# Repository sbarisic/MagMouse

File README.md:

# MagMouse

An open-source wired mouse exploring contactless Hall-sensed buttons with plastic
click mechanisms, and a motorized haptic scroll wheel.

**Active development: [three two-layer boards](hardware/two-layer/sandwich/README.md),
with two 70 Ã— 100 mm stacked Main boards and passive plastic button clicks.**
All three boards are routed, with independent schematics and clean native
ERC, DRC, connectivity and schematic-parity checks under the saved rules.
The [quote package](hardware/two-layer/sandwich/quote-package/README.md) contains
Gerbers, drills, BOMs and placement files; supplier and physical acceptance remain open.
The Main stack and Wheel harness each use 19 wires with three shared grounds.

Superseded boards, bench fixtures and quote packages are available in
[Git history](docs/history/README.md). The current checkout contains the active
designs, shared libraries, current manufacturing exports and retained evidence.

## V1 concept

- ESP32-S3 with native USB Full-Speed HID; target report interval: 1 ms.
- PMW3360DM-T2QU + LM19-LSI optical sensor for cursor movement; ICM-42688-P for supplementary motion.
- Three plastic click mechanisms provide tactile feedback and passive return.
  Each uses a TMAG5253 Hall sensor and a sensing magnet, read through ADS7038.
  Buttons have no coils or powered force feedback.
- GB1806 motor with integrated AS5048A angle sensing driven by DRV8316R for scroll haptics.
- One USB-C cable for data and 5 V power, with force limits based on detected
  source capability. A powered Type-C hub/adapter is the intended full-power source.

## Repository map

| Directory | Contents |
| --- | --- |
| [hardware](hardware/README.md) | Electronics, preliminary BOM, schematic and PCB work |
| [mechanical](mechanical/README.md) | Housing, button mechanisms, scroll assembly |
| [firmware](firmware/README.md) | Embedded architecture and bring-up plan |
| [software](software/README.md) | Future PC configuration application |
| [docs](docs/README.md) | Requirements, interfaces, power and roadmap |

Start with the [architecture](docs/architecture.md), [interface plan](docs/interfaces.md),
and [button prototype plan](mechanical/button-mechanisms/README.md), then the
[roadmap](docs/roadmap.md). [ideas.md](ideas.md) preserves the original
brainstorming notes; the organized documents distinguish selected directions from
open engineering questions.

## Contributing and licensing

See [CONTRIBUTING.md](CONTRIBUTING.md). The next milestone is mechanical-interface
CAD, resulting PCB adjustments and whole-board review before manufacturing closure.

Hardware/mechanical: **CERN-OHL-S-2.0**. Firmware, PC software and supporting code:
**GPL-3.0-or-later**. General documentation: **CC-BY-SA-4.0**.
See [LICENSE.md](LICENSE.md) for scope and full texts.

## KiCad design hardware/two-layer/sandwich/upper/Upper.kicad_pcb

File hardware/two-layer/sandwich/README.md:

# MagMouse stacked two-layer boards

The GB1806 now includes an AS5048A encoder. The separate magnet-axis board and
37 bottom test pads are removed. See [encoder integration](ENCODER_INTEGRATION.md)
for the revised power circuit, wiring, timing and bring-up checks.

The subsequent [routing cleanup](routing-cleanup-review.json) covers Lower,
Upper and Wheel, including USB fanouts. It removes exposed sharp bends and
repeated stair-step runs, retains the wide USB pair and transition vias, and
checks full-width opposite-layer ground coverage. `validate_routing_cleanup.py`
checks this geometry as well as native DRC, connectivity and schematic parity.
The bend inventory includes width transitions and excludes pad/via interiors
and branch junctions. Single clearance offsets and the paired USB width
transitions remain; repeated short alternating turns are rejected. The cleanup
retains all component positions and original vias and adds one Lower ground stitch.

The three boards are routed and have independent schematics. Native KiCad 10.0.6
checks report zero ERC findings, DRC findings, unconnected items and schematic
parity findings under the saved rules. The [quote package](quote-package/README.md)
contains the files for supplier pricing; physical and supplier acceptance remain open.

The active boards use 1206 packages for all 205 resistors and ceramic capacitors.
The encoder revision changes C55/C64 to 1 µF and adds C105; other passive values
retain the reviewed circuit revisions.
[1206-PARTS.md](1206-PARTS.md) lists the replacement manufacturer part numbers,
ratings and sourcing status. [1206-review.json](1206-review.json) records the
earlier package migration; [assembly-spacing-review.json](assembly-spacing-review.json)
records the subsequent 2 mm component spacing and outline changes.

The standard-via revision uses 0.30 mm via drills and at least 0.45 mm copper
lands. All three boards are checked for via-hole/SMD-land overlaps. The derived
[238 × 114 mm panel](panel/Panel.kicad_pcb) combines one of each board using
2 mm routed gaps and 5 mm mouse-bite tabs. Source copper is copied exactly,
with isolated net names for each board; individual outlines remain unchanged.

All three boards require 0.5 mm copper clearance to their outer edges.
Lower's internal optical aperture retains a reviewed 0.4 mm clearance, enforced
by a custom rule for the `Optical aperture` edge group; the panel carries the same
exception. Outlines and the 2 mm assembly spacing remain unchanged. Only C55/C64
move to make room for the new local encoder regulator; C105 occupies C64's former location.

Full manufacturing panel: [top copper](panel/Panel-top.png) and
[bottom copper, viewed from underneath](panel/Panel-bottom.png).
Both show traces, filled zones, pads, vias and silkscreen.

| Board/project | Dimensions | Copper layers | Total footprints |
| --- | --- | ---: | ---: |
| [Lower](lower/Lower.kicad_pro) | 70 × 100 mm, tapered | 2 | 100 |
| [Upper](upper/Upper.kicad_pro) | 70 × 100 mm, tapered | 2 | 85 |
| [Wheel](wheel/Wheel.kicad_pro) | 70 × 67 mm, clipped Main profile | 2 | 96 |

[All-board overview](all-boards.png). Component footprints, pads and drills are
full size. Both Main outlines retain the approved taper and 38.5 mm front edge.
Wheel follows the Main sidewalls between y = 26 and 93 mm. Its 4,448 mm² outline adds 1,148 mm² to the previous rectangle. Wheel coordinates plus (7.5, 29) mm align it with Main in plan view. Stack height and Wheel mounting need mechanical fit confirmation.

[Wheel power and ground review](routing-review/POWER-GROUND.md) covers trace necks, via barrels, GND pours and the reordered brake feedback resistors.

[3D exports](3d/README.md) include STEP, GLB and angled previews for each board
and the panel, plus bare substrate STEP files. The populated exports include
available library models; the coverage report identifies 13 missing component
bodies. These are PCB models, not a mechanically positioned mouse assembly.

## Circuit and schematic split

Lower contains the ESP32, USB connector and data/CC circuitry, 3.3 V regulator,
optical sensor and local supplies, IMU, RGB, encoder interface and Wheel signal
connector J8. Upper contains the eFuses, power monitoring, three Hall sensors,
ADC1, hardware interlock and Wheel power connector J10.

The independent [Lower schematic](lower/Lower.kicad_sch) and
[Upper schematic](upper/Upper.kicad_sch) each include `20_Stack_Harness` with the
actual signal/power arrays and mounting holes. PCB symbol paths match these
projects. The combined [Main circuit](main-circuit/Main.kicad_sch) is retained as
the migration reference; edit the independent projects for subsequent work.
Every retained component value and pin/net connection was compared with that
reference. USB data/CC and analog Hall/current-sense/ADC connections stay local
to their respective boards.

Buttons use passive plastic click mechanisms and one sensing magnet per Hall
sensor. The active design removes 38 button-only parts, including U4/U5/U6,
J2/J3/J4 and U17. ADC1 channels 3–5 are grounded spares; GPIO4–9 are unused.
U18 retains the shared HALL_EN gate. Wheel drive, interlock, ACT_5V protection
and shared storage remain. [passive-buttons.json](passive-buttons.json) records
the exact removed parts and pin changes. The older routed checkpoints retain
the superseded button-coil circuitry.

## Wiring

The Main stack has **19 wires with three shared grounds**:

| Interface | Signals/supplies | Grounds | Total |
| --- | ---: | ---: | ---: |
| J101 ↔ J102 | 13 signals | 1 | 14 |
| J103 ↔ J104 | 3 supply rails | 2 | 5 |

Connect equal pad numbers using [WIRE_MAP.md](WIRE_MAP.md). Signal arrays are
2 × 7 at 2.54 mm pitch: x = 6/8.54 mm, y = 42–57.24 mm, 1.8 mm lands and
0.8 mm drills. Five power pads use 5.08 mm pitch at x = 25–45.32 mm,
2.4 mm lands and 1.2 mm drills. Both power arrays moved together to y = 12.25 mm
to provide assembly space below USB. Raw VBUS goes up, PWR_5V returns to Lower and
+3V3 goes back up. ACT_5V stays on Upper and feeds Wheel.

The Wheel harness also has **19 wires with three shared grounds**. Lower J8
and Wheel J9 each use 17 pads in a 2 × 9 grid with one hole omitted; their copper
envelope is 22.12 × 4.34 mm. Upper J10 and Wheel J11 carry ACT_5V and the third
ground. See [WHEEL_WIRE_MAP.md](WHEEL_WIRE_MAP.md). Wire gauges, cut lengths and
stack height still depend on the mechanical assembly.

## Placement and routing

Separate front components have at least 2 mm between their body-and-solder-land
envelopes. This does not change the pitch of pins within an IC or wire array;
copper-only test access is excluded from the component spacing measurement.
The circled Upper passive group has at least 3 mm clearance to the board edge.
The layouts retain the USB, optical, antenna and mounting datums. The Hall
sensors now follow the three user-marked front locations; see
[Hall placement](HALL_PLACEMENT.md). The two stack power arrays retain their
pin map; matching pin 3 moves clear of the centre Hall sensor.
Other parts and colliding front test pads move as recorded in the spacing review.
Fitted electronic parts remain on the front; all 37 underside diagnostic test pads have been removed. Six top-side test pads remain. The standalone Encoder PCB has been removed; the motor supplies its own AS5048A encoder.

The lower USB pair runs just to the right of the optical opening. Both USB-C
orientations use two paired layer changes with nearby GND stitching. A check
against filled copper found GND opposite the full trace width from the connector
through the MCU escapes, outside the signal vias' own clearances. The previous
wide traces crossed 35.45 mm (D+) and 42.34 mm (D−) without GND beneath their
centerlines. Connector-to-series-resistor lengths are now 80.94–82.42 mm.
See the [USB and power comparison](routing-review/lower-usb-placement.png),
[layer-by-layer GND view](routing-review/lower-usb-ground.png) and
[measured paths and placement changes](routing-review/lower-usb.json).

Repositioning the RGB regulator, optical buffer and nearby parts shortened the
5 V buck feed to 23.70 mm and the optical-buffer feed to 32.15 mm. The RGB
regulator feed gained 2.21 mm and two vias. The status LED D5 moved to
(52.925, 36.48) mm. Check its case/light-pipe alignment and confirm USB
differential impedance against the fabricator's stackup before ordering.
Host SPI clock and data nets grew in total branched length. Check their
waveforms at the intended clock rate on the first assembly.

The subsequent three-board routing check removed same-layer loops and duplicate
tracks on Lower, Upper and Wheel. The pictured Lower SPI MOSI run is now a
single diagonal. See the [panel Gerber comparison](routing-review/wheel-lower-trace-cleanup.png)
and the [board-by-board results](routing-review/trace-loop-review.json).

Aligned M2 mounting candidates remain at (18,6), (52,6), (7,76), (63,76) mm:
2.2 mm holes and 5 mm support envelopes. Lower now has a real 17.26 × 8.60 mm
optical opening on Edge.Cuts, following PixArt PMW3360 datasheet R1.50 Figure 3.
In board coordinates it spans x = 31.20–39.80 and y = 43.68–60.94 mm; U35's
optical center remains (35.5,52.5) mm. Internal corners use R1 mm for the panel's
nominal 2 mm router; this corner geometry requires lens-fit confirmation.
The lens faces downward through Lower,
so this does not add a duplicate opening to Upper. Lens retention and stack
height still need mechanical fit confirmation. U3 stays at (35,89.25) mm,
with its antenna approximately 0.43 mm from
the curved board edge at the corners. The requested 5 mm reserve is
x = 22.3–47.7, y = 94.5–104 mm on both boards, extending beyond the rear edge.
Upper retains substrate over that region; assembled radio performance is untested.

## Validation and quote files

[routing-review/summary.json](routing-review/summary.json) records current board
hashes, sizes, layer counts, ERC/DRC/parity results and fabrication dimensions.
The native reports, exported netlists, front/back copper SVGs and track-width
measurements are alongside it. Inherited ignored categories remain explicit in
the reports; no new DRC or ERC exclusions were added for routing.

[quote-package](quote-package/) contains three separate Gerber/drill ZIPs,
per-board BOM/CPL CSVs, combined purchasing inventory, manual items and
via-in-pad intersection lists. The redundant whole-package archive is removed;
the individual fabrication ZIPs and [panel](panel/) remain. Read the [quotation notes](quote-package/README.md)
for stack, assembly, stock, shipping/tax and mechanical assumptions. This is a
pricing package. The [first live quote](quotes/2026-11-04-jlcpcb/QUOTE.md) records
the superseded 0.20 mm, separate-board version. The [standard-via panel quote](quotes/2026-11-04-panel-standard-vias/QUOTE.md)
was EUR 42.83 for five complete sets, or USD 99.25 delivered by EuroPacket DDP
to Croatia (4 November 2026). That quote predates the 1206 migration and has not
been refreshed for these files. No fabrication order is placed.

`partition.json` preserves ownership and the checked 19-wire contract.
`placement-positions.json`, `spacing-review.json`, `spacing-baseline.json`,
`placement.svg/png` and `passive-validation.json` are historical pre-routing
evidence; their old board hashes and airwire counts are not current route results.
`hall-relocation.json` records the later requested sensor and wire-pad moves.
`hall-placement-review.json` and `hall-routing-review.json` contain their current
placement, bypass, power-path and routing checks. Run `validate_hall.py` after
future routing changes; its checks retain the earlier geometry and rule baselines.

## Reproduction

The [November circuit correction review](circuit-review/README.md) records the
powered-off buffer substitutions, local motor undervoltage inhibit and capacitor
placement changes. `validate_circuit_fixes.py` checks their explicit allowlist,
all five harness pairs, spacing and via constraints. The historical combined
schematic is deliberately unchanged. Firmware and bench acceptance remain open.

Use KiCad 10 Python. Edit the independent KiCad projects for future circuit or
layout changes. The one-time split and obsolete placement generators are now
in [Git history](../../../docs/history/README.md). Shared libraries and helper
functions live in [hardware/common](../../common/README.md).

`route_main.py` exports/imports Specctra sessions, `route_usb.py` defines the
initial USB corridor, `finish_main.py` fills and stitches ground, and
`widen_power.py` widens power where clearance and keepouts allow. Freerouting
2.5.0 used neck retry at 150 µm with the optimizer disabled for Lower. Lower's
DSN clearance was increased to 165 µm to leave margin for native minimum-width
restoration; saved KiCad clearances remain unchanged. Temporary sessions, router
binaries and logs stay in ignored `build/sandwich/main-routing`.

`export_quote.py` rechecks all three boards before exporting the package and
compares Main pins against the retained migration reference. `overview.py`
renders placement views; add `--main-only --copper` for the routed Main image.
The netlist and schematic-parity checks cover the current Wheel harness.
The obsolete harness conversion script is retained in Git history.

`standard_vias.py` records the one-time drill migration and assists local via
relocation; `repair_wheel.py` and `continuous_routes.py` provide local path repairs.
`standard-via-review.json` is historical evidence for the pre-1206 revision. It records unchanged component placement and pad/net identity,
unchanged motor-phase/brake copper, and the final drill and via-in-pad counts. The finished
KiCad boards are the editable source. `panelize.py` derives and verifies the
combined manufacturing panel and exports its Gerbers/drills. Its verification
compares every source pad, track, via drill and filled-zone vertex after translation,
checks connected substrate and router access, and runs native panel DRC.

`large_passives.py` performs the guarded one-time 1206 migration and verifies it
against the saved pre-migration snapshots in ignored `build/sandwich/1206`.
`1206-migration.json` records the per-reference purchasing substitutions;
`1206-review.json` records the final checks and source hashes. Do not rerun
the migration on an already converted project. `region_routes.py` supports
local two-layer repairs; every saved result still requires native KiCad DRC.

The fabrication rules explicitly use JLCPCB's 0.075 mm via annular ring and
0.20 mm via-hole-to-copper clearance, replacing 0.125/0.25 mm in the earlier
revision. Via hole-to-hole clearance stays 0.25 mm, copper clearance stays
0.15 mm by net class (0.127 mm board minimum), and minimum track width stays
0.127 mm. No additional DRC categories are ignored. These limits are based on
[JLCPCB's published capabilities](https://jlcpcb.com/capabilities/pcb-capabilities/).

Hardware: CERN-OHL-S-2.0. Scripts: GPL-3.0-or-later. Documentation: CC-BY-SA-4.0.

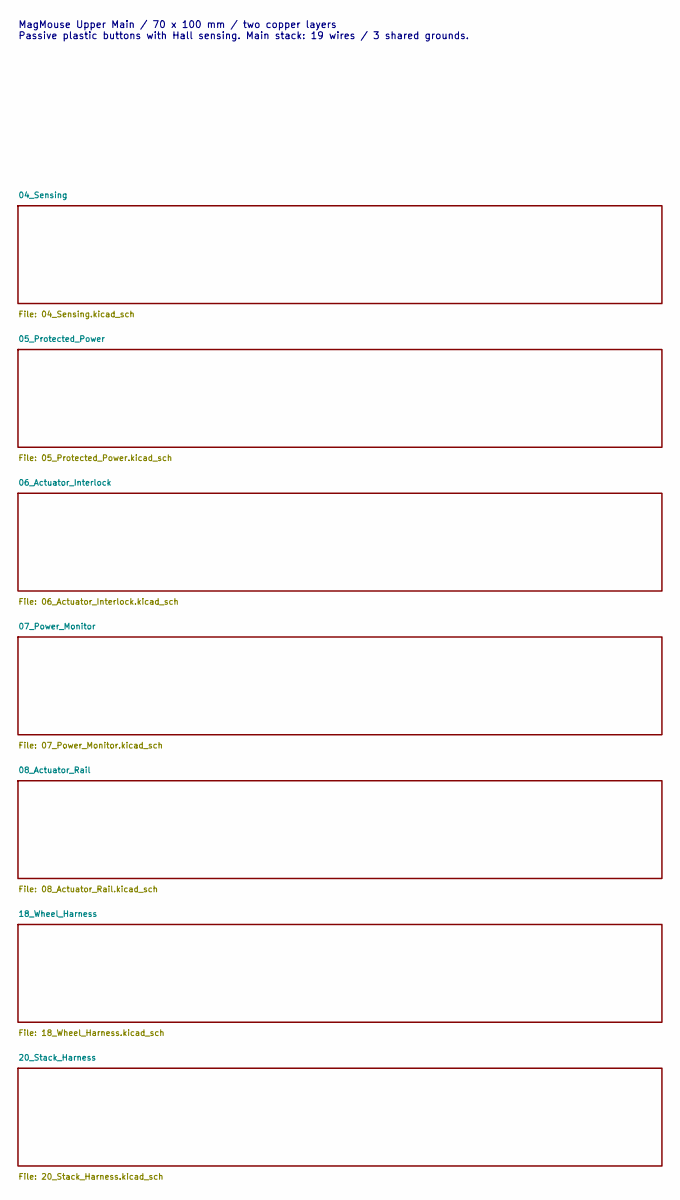
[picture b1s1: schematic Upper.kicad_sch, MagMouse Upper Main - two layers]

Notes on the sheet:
MagMouse Upper Main / 70 x 100 mm / two copper layers Passive plastic buttons with Hall sensing. Main stack: 19 wires / 3 shared grounds.

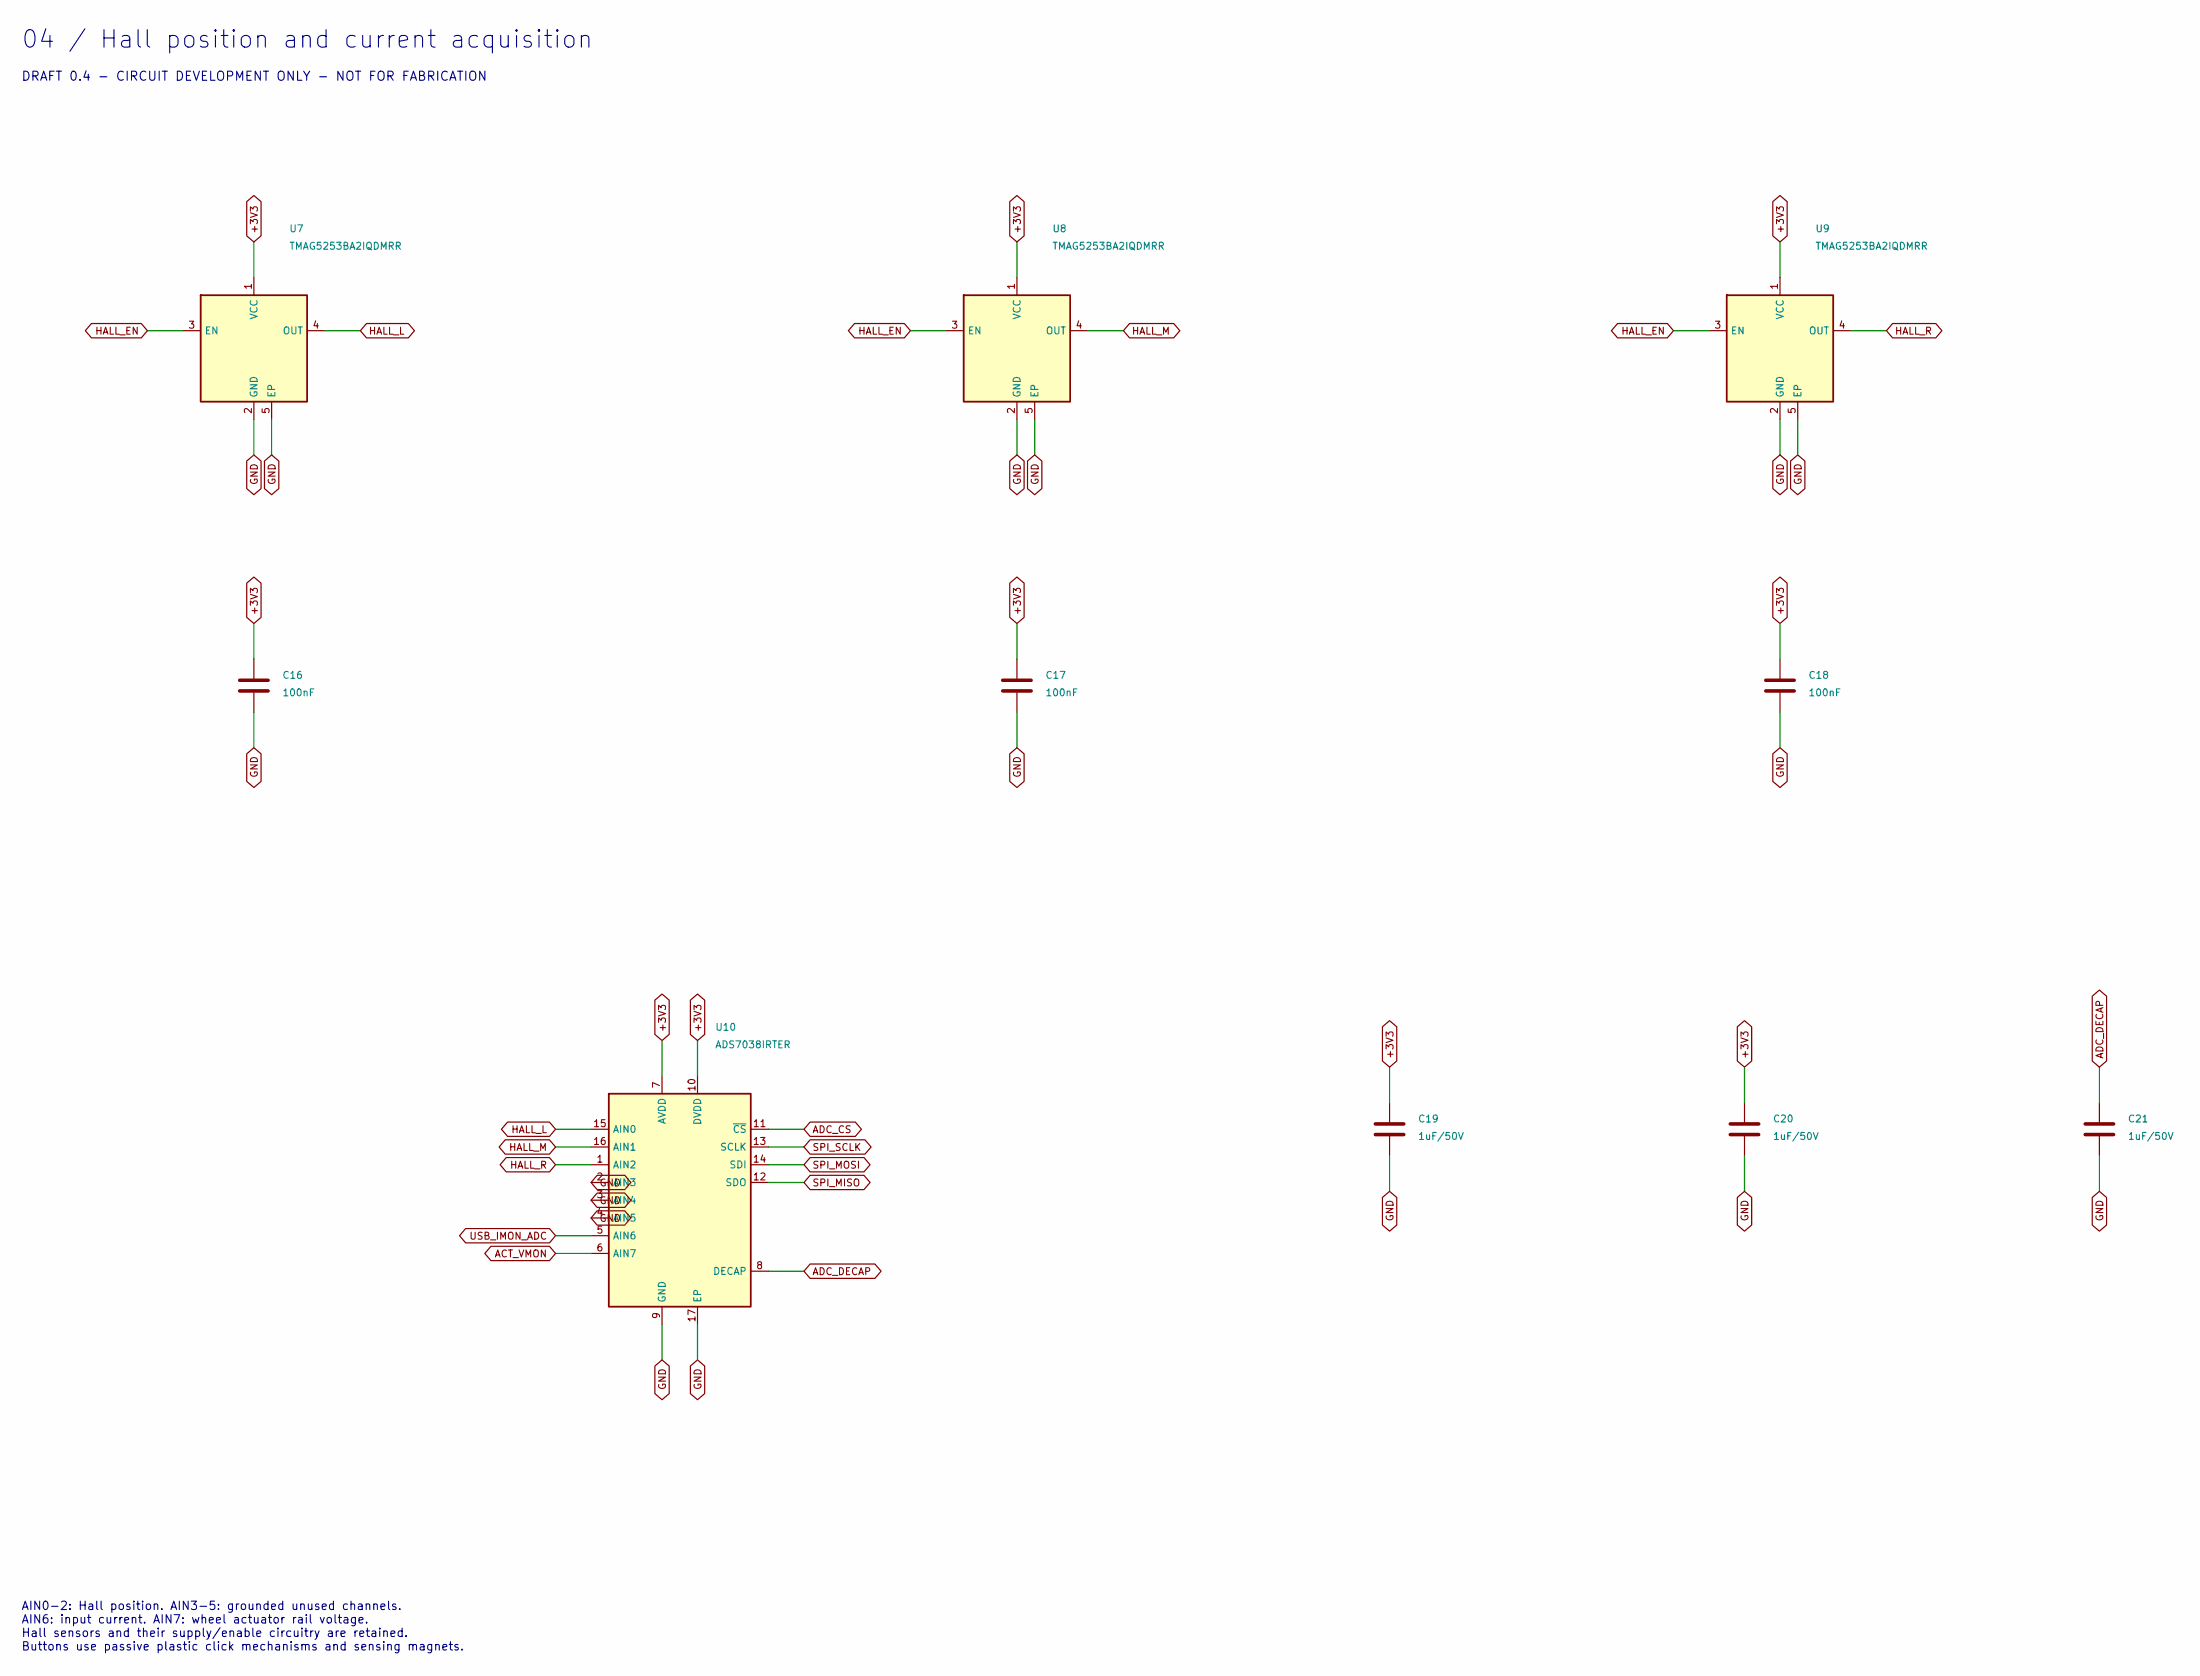
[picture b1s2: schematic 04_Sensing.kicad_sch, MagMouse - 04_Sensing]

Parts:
C16, C17, C18: 100nF; C_1206_3216Metric; Rating 50 V, X7R, 10%; MPN CC1206KRX7R9BB104
C19, C20, C21: 1uF/50V; C_1206_3216Metric; Rating 50 V, X7R, 10%; MPN CL31B105KBHNNNE; JLCPCB Library Type Basic
U7, U8, U9: TMAG5253BA2IQDMRR; Texas_X2SON-4-1EP_1.1x1.4mm_P0.5mm_EP0.8x0.6mm; MPN TMAG5253BA2IQDMRR; LCSC C35414983
U10: ADS7038IRTER; WQFN-16-1EP_3x3mm_P0.5mm_EP1.68x1.68mm; MPN ADS7038IRTER; LCSC C2871580

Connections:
+3V3: C16.1, C17.1, C18.1, C19.1, C20.1, U7.1 (VCC), U8.1 (VCC), U9.1 (VCC), U10.7 (AVDD), U10.10 (DVDD); also elsewhere on the board
ACT_VMON: U10.6 (AIN7); also elsewhere on the board
ADC_CS: U10.11 (~CS); also elsewhere on the board
ADC_DECAP: C21.1, U10.8 (DECAP)
GND: C16.2, C17.2, C18.2, C19.2, C20.2, C21.2, U7.2 (GND), U7.5 (EP), U8.2 (GND), U8.5 (EP), U9.2 (GND), U9.5 (EP), U10.2 (AIN3), U10.3 (AIN4), U10.4 (AIN5), U10.9 (GND), U10.17 (EP); also elsewhere on the board
HALL_EN: U7.3 (EN), U8.3 (EN), U9.3 (EN); also elsewhere on the board
HALL_L: U7.4 (OUT), U10.15 (AIN0)
HALL_M: U8.4 (OUT), U10.16 (AIN1)
HALL_R: U9.4 (OUT), U10.1 (AIN2)
SPI_MISO: U10.12 (SDO); also elsewhere on the board
SPI_MOSI: U10.14 (SDI); also elsewhere on the board
SPI_SCLK: U10.13 (SCLK); also elsewhere on the board
USB_IMON_ADC: U10.5 (AIN6); also elsewhere on the board

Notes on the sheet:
04 / Hall position and current acquisition
DRAFT 0.4 - CIRCUIT DEVELOPMENT ONLY - NOT FOR FABRICATION
AIN0-2: Hall position. AIN3-5: grounded unused channels. AIN6: input current. AIN7: wheel actuator rail voltage. Hall sensors and their supply/enable circuitry are retained. Buttons use passive plastic click mechanisms and sensing magnets.

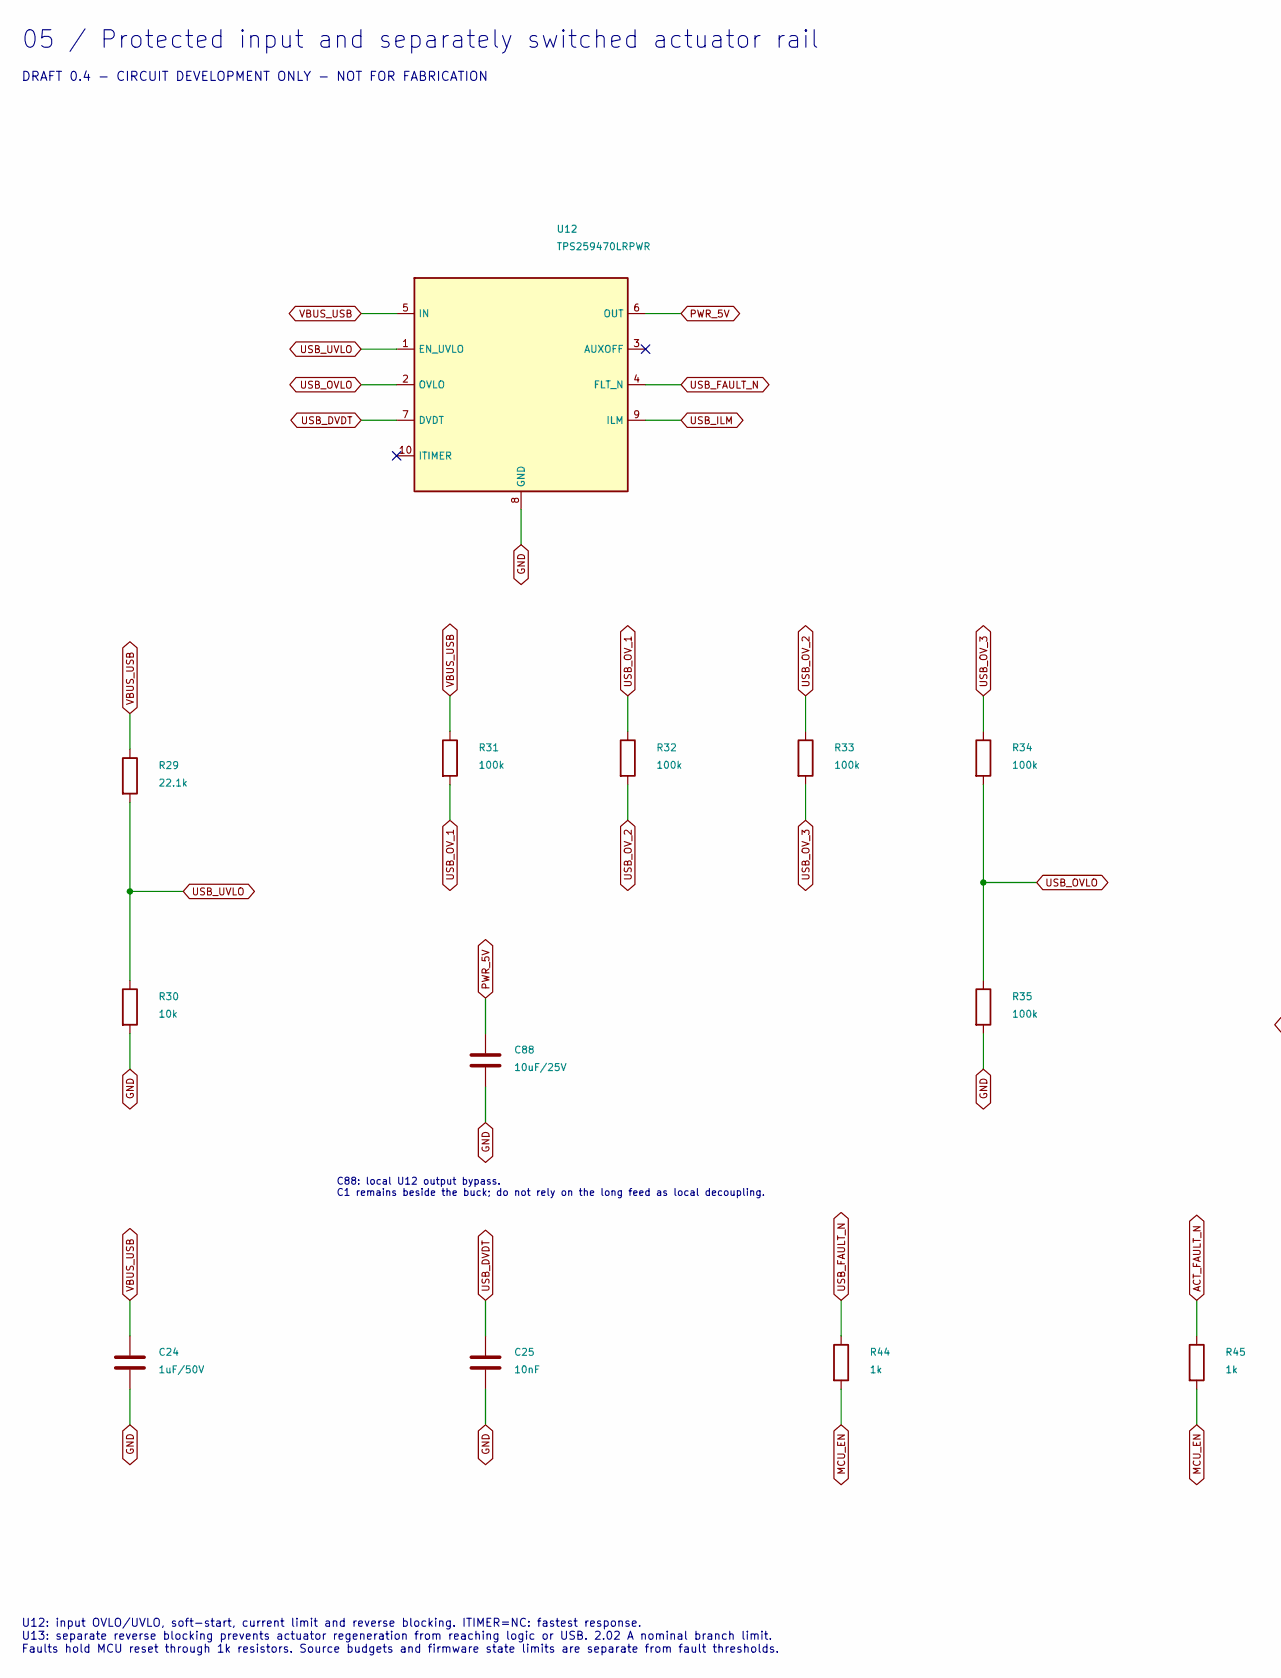
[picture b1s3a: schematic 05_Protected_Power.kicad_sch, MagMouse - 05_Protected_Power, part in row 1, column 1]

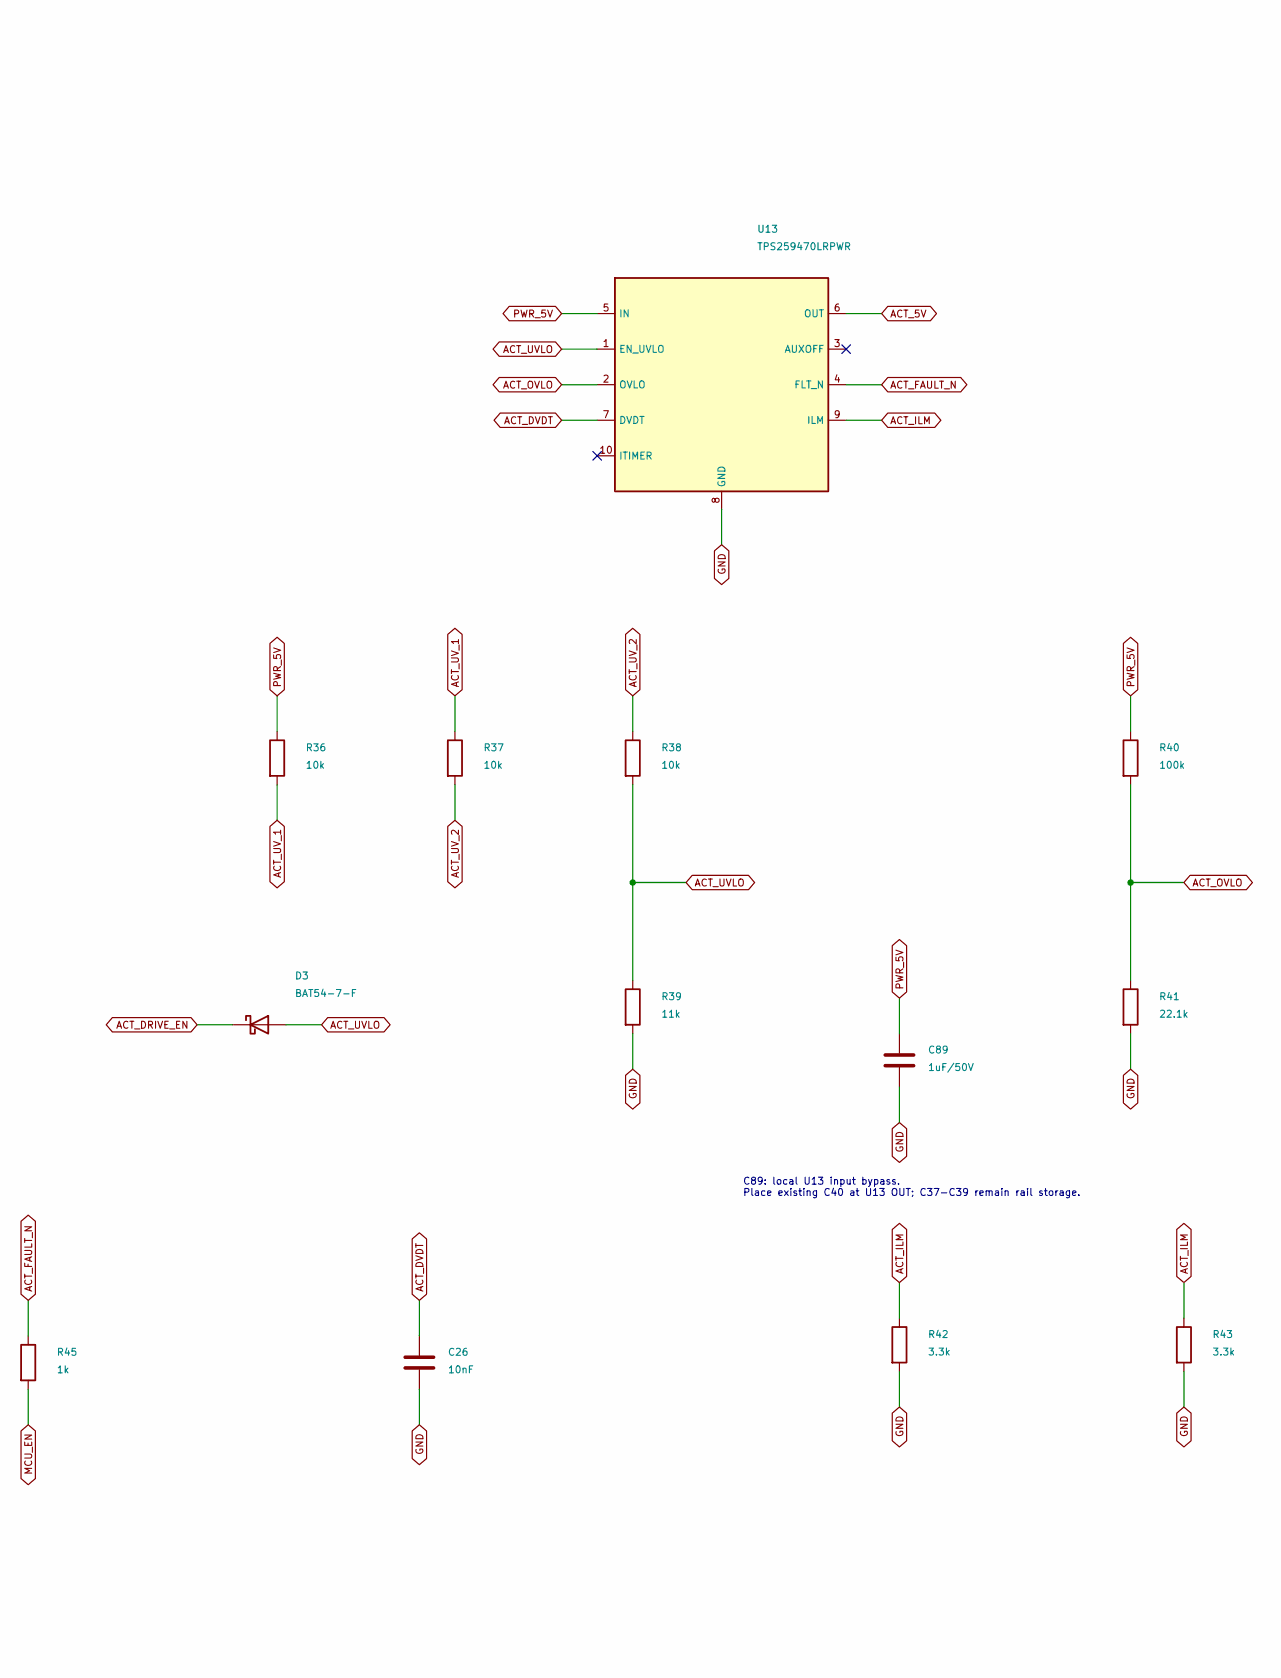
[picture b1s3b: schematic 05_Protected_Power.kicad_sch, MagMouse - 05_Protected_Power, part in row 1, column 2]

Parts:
C24, C89: 1uF/50V; C_1206_3216Metric; Rating 50 V, X7R, 10%; MPN CL31B105KBHNNNE
C25, C26: 10nF; C_1206_3216Metric; Rating 50 V, X7R, 10%; MPN CC1206KRX7R9BB103
C88: 10uF/25V; C_1206_3216Metric; Rating 25 V, X5R, 10%; MPN CL31A106KAHNNNE
D3: BAT54-7-F; SOT-23; MPN BAT54-7-F; LCSC C106920
R29, R41: 22.1k; R_1206_3216Metric; Rating 0.25 W, 1%; MPN RC1206FR-0722K1L
R30, R36, R37, R38: 10k; R_1206_3216Metric; Rating 0.25 W, 1%; MPN RC1206FR-0710KL
R31, R32, R33, R34, R35, R40: 100k; R_1206_3216Metric; Rating 0.25 W, 1%; MPN RC1206FR-07100KL
R39: 11k; R_1206_3216Metric; Rating 0.25 W, 1%; MPN RC1206FR-0711KL
R42, R43: 3.3k; R_1206_3216Metric; Rating 0.25 W, 1%; MPN RC1206FR-073K3L
R44, R45: 1k; R_1206_3216Metric; Rating 0.25 W, 1%; MPN RC1206FR-071KL
U12, U13: TPS259470LRPWR; Texas_RPW0010A; MPN TPS259470LRPWR; LCSC C3662793

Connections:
ACT_5V: U13.6 (OUT); also elsewhere on the board
ACT_DRIVE_EN: D3.3 (K); also elsewhere on the board
ACT_DVDT: C26.1, U13.7 (DVDT)
ACT_FAULT_N: R45.1, U13.4 (FLT_N)
ACT_ILM: R42.1, R43.1, U13.9 (ILM)
ACT_OVLO: R40.2, R41.1, U13.2 (OVLO)
ACT_UVLO: D3.1 (A), R38.2, R39.1, U13.1 (EN_UVLO)
ACT_UV_1: R36.2, R37.1
ACT_UV_2: R37.2, R38.1
GND: C24.2, C25.2, C26.2, C88.2, C89.2, R30.2, R35.2, R39.2, R41.2, R42.2, R43.2, U12.8 (GND), U13.8 (GND); also elsewhere on the board
MCU_EN: R44.2, R45.2; also elsewhere on the board
PWR_5V: C88.1, C89.1, R36.1, R40.1, U12.6 (OUT), U13.5 (IN); also elsewhere on the board
USB_DVDT: C25.1, U12.7 (DVDT)
USB_FAULT_N: R44.1, U12.4 (FLT_N)
USB_ILM: U12.9 (ILM); also elsewhere on the board
USB_OVLO: R34.2, R35.1, U12.2 (OVLO)
USB_OV_1: R31.2, R32.1
USB_OV_2: R32.2, R33.1
USB_OV_3: R33.2, R34.1
USB_UVLO: R29.2, R30.1, U12.1 (EN_UVLO)
VBUS_USB: C24.1, R29.1, R31.1, U12.5 (IN); also elsewhere on the board

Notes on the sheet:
05 / Protected input and separately switched actuator rail
DRAFT 0.4 - CIRCUIT DEVELOPMENT ONLY - NOT FOR FABRICATION
U12: input OVLO/UVLO, soft-start, current limit and reverse blocking. ITIMER=NC: fastest response. U13: separate reverse blocking prevents actuator regeneration from reaching logic or USB. 2.02 A nominal branch limit. Faults hold MCU reset through 1k resistors. Source budgets and firmware state lim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
C88: local U12 output bypass. C1 remains beside the buck; do not rely on the long feed as local decoupling.
C89: local U13 input bypass. Place existing C40 at U13 OUT; C37-C39 remain rail storage.

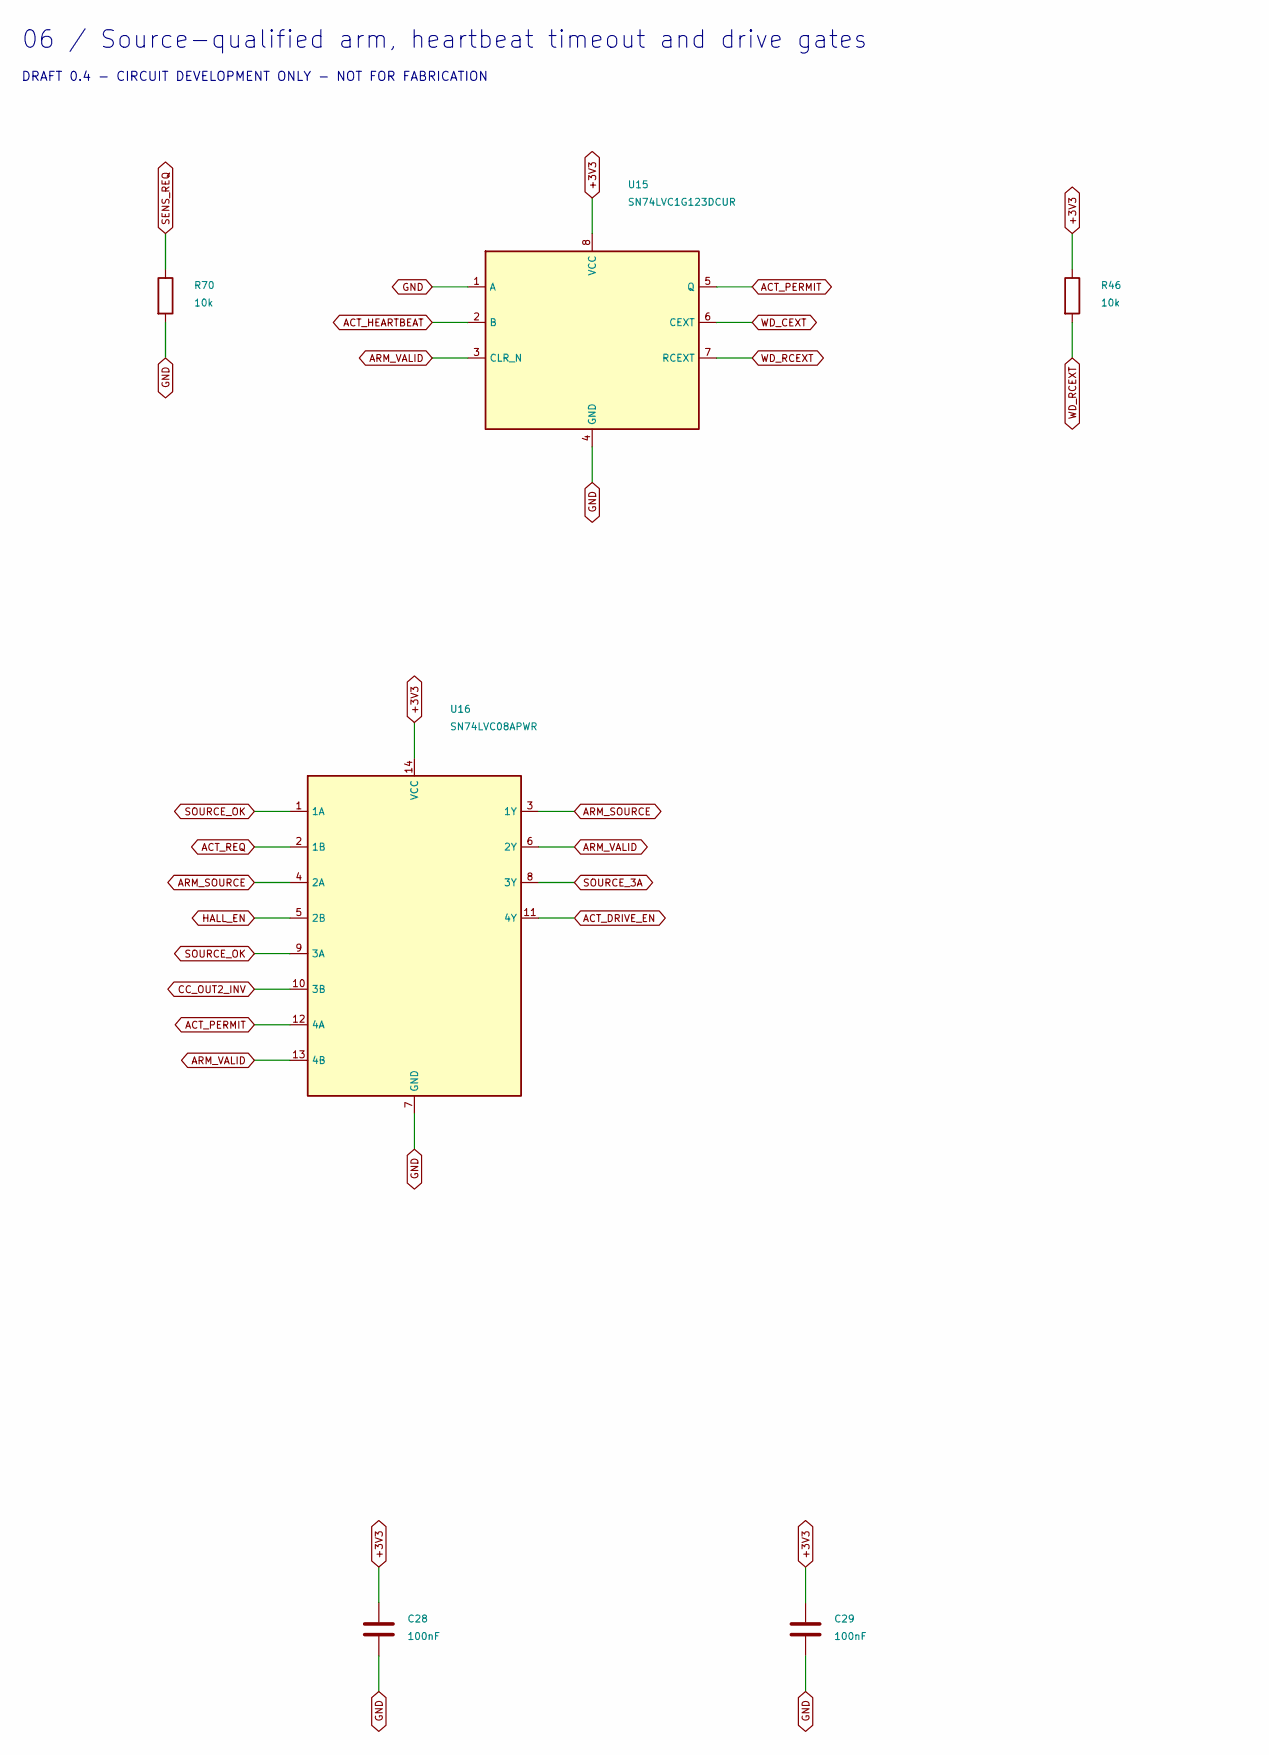
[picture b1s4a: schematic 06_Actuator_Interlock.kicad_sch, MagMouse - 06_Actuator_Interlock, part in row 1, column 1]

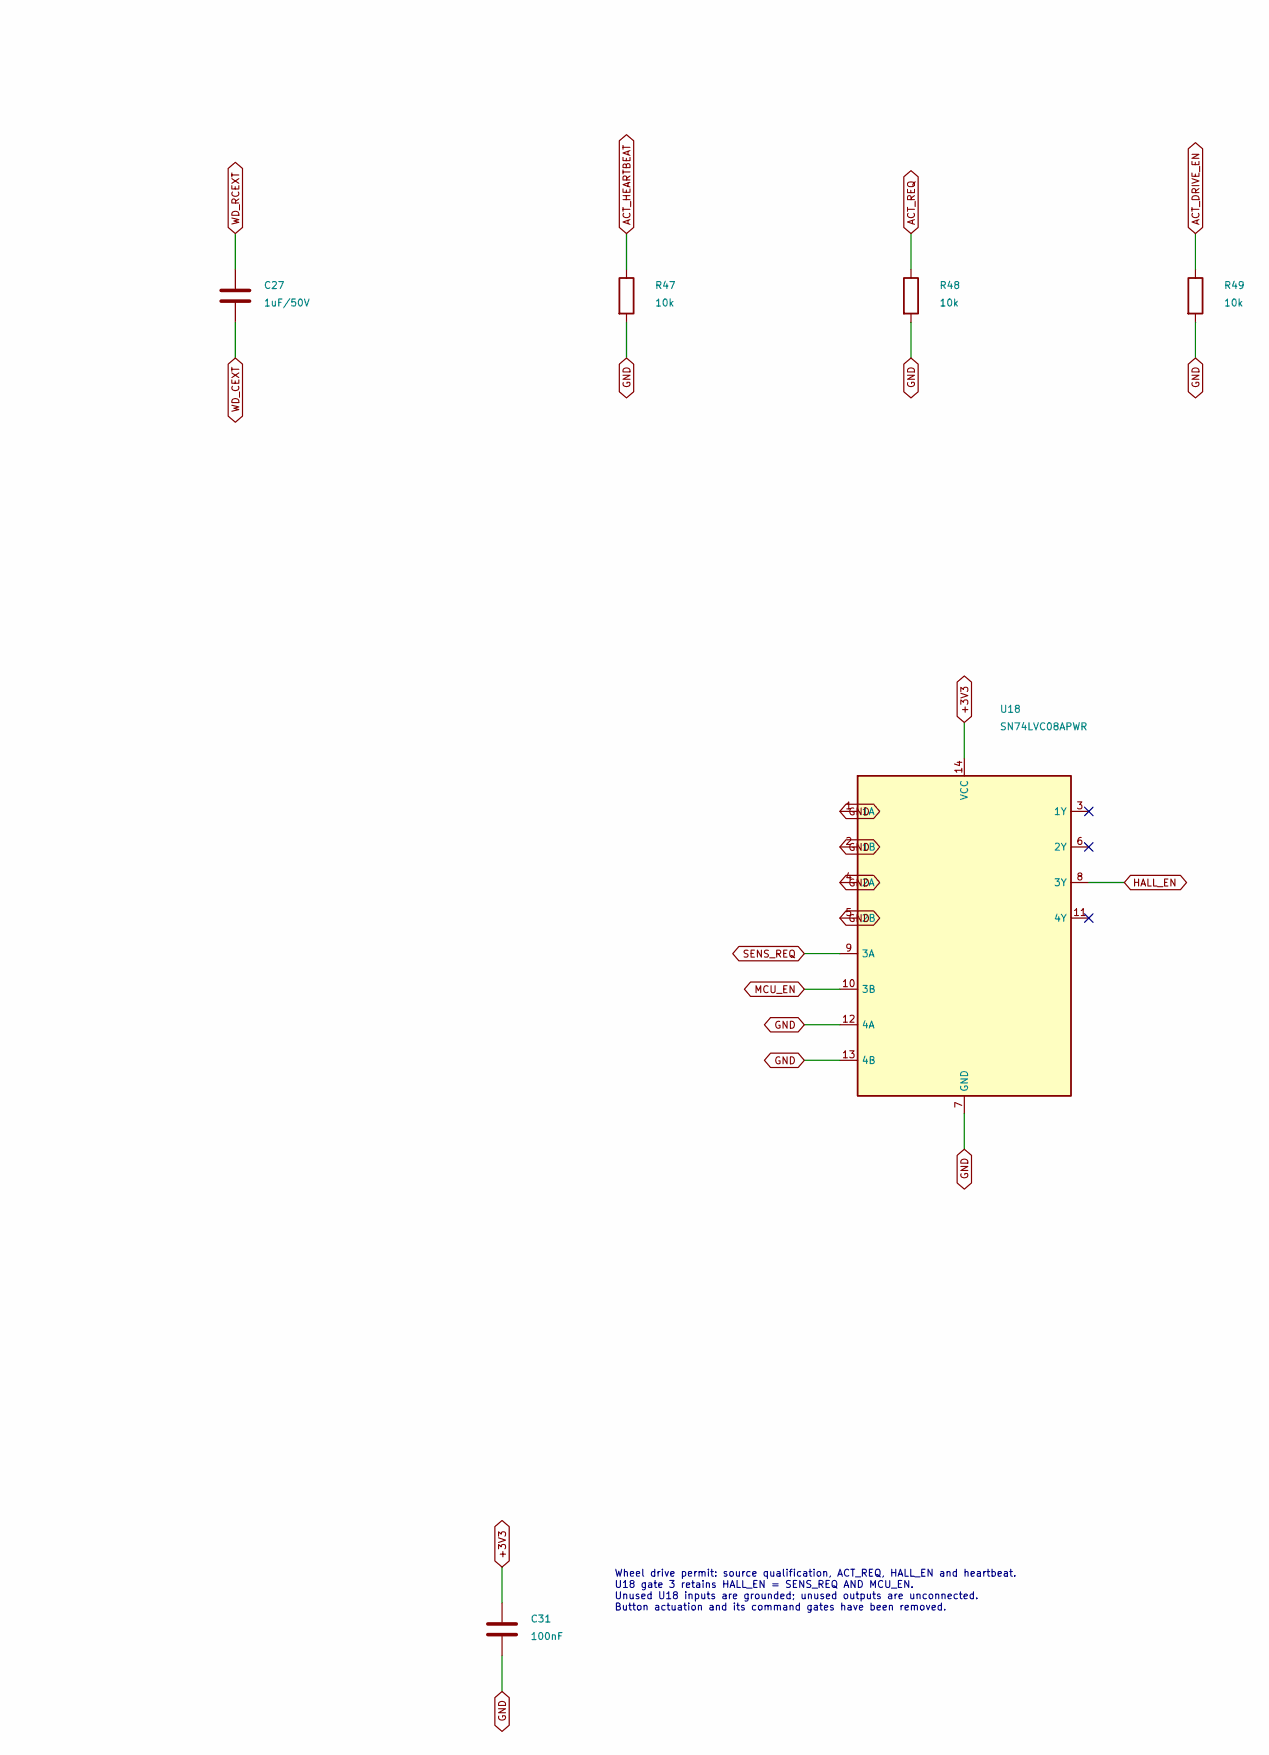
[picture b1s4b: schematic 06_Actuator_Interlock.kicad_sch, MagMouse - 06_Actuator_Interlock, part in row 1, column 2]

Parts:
C27: 1uF/50V; C_1206_3216Metric; Rating 50 V, X7R, 10%; MPN CL31B105KBHNNNE
C28, C29, C31: 100nF; C_1206_3216Metric; Rating 50 V, X7R, 10%; MPN CC1206KRX7R9BB104
R46, R47, R48, R49, R70: 10k; R_1206_3216Metric; Rating 0.25 W, 1%; MPN RC1206FR-0710KL
U15: SN74LVC1G123DCUR; VSSOP-8_2.3x2mm_P0.5mm; MPN SN74LVC1G123DCUR; LCSC C352969
U16, U18: SN74LVC08APWR; TSSOP-14_4.4x5mm_P0.65mm; MPN SN74LVC08APWR; LCSC C465737

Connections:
+3V3: C28.1, C29.1, C31.1, R46.1, U15.8 (VCC), U16.14 (VCC), U18.14 (VCC); also elsewhere on the board
ACT_DRIVE_EN: R49.1, U16.11 (4Y); also elsewhere on the board
ACT_HEARTBEAT: R47.1, U15.2 (B); also elsewhere on the board
ACT_PERMIT: U15.5 (Q), U16.12 (4A)
ACT_REQ: R48.1, U16.2 (1B); also elsewhere on the board
ARM_SOURCE: U16.3 (1Y), U16.4 (2A)
ARM_VALID: U15.3 (CLR_N), U16.6 (2Y), U16.13 (4B)
CC_OUT2_INV: U16.10 (3B); also elsewhere on the board
GND: C28.2, C29.2, C31.2, R47.2, R48.2, R49.2, R70.2, U15.1 (A), U15.4 (GND), U16.7 (GND), U18.1 (1A), U18.2 (1B), U18.4 (2A), U18.5 (2B), U18.7 (GND), U18.12 (4A), U18.13 (4B); also elsewhere on the board
HALL_EN: U16.5 (2B), U18.8 (3Y); also elsewhere on the board
MCU_EN: U18.10 (3B); also elsewhere on the board
SENS_REQ: R70.1, U18.9 (3A); also elsewhere on the board
SOURCE_3A: U16.8 (3Y); also elsewhere on the board
SOURCE_OK: U16.1 (1A), U16.9 (3A); also elsewhere on the board
WD_CEXT: C27.2, U15.6 (CEXT)
WD_RCEXT: C27.1, R46.2, U15.7 (RCEXT)

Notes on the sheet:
06 / Source-qualified arm, heartbeat timeout and drive gates
DRAFT 0.4 - CIRCUIT DEVELOPMENT ONLY - NOT FOR FABRICATION
Wheel drive permit: source qualification, ACT_REQ, HALL_EN and heartbeat. U18 gate 3 retains HALL_EN = SENS_REQ AND MCU_EN. Unused U18 inputs are grounded; unused outputs are unconnected. Button actuation and its command gates have been removed.
